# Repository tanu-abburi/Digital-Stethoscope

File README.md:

# Digital Stethoscope  
A **digital stethoscope** that amplifies, filters, and digitally processes heart sounds for enhanced diagnostics and remote monitoring.  
## Project Outline
We intend on developing a digital stethoscope system which includes an acoustic sensor that is attached to the processing unit, which will catch the signal, amplify it using an amplifier circuit using an op amp TL082.
The amplified signal is then sent to the ATMEGA328-P, which then converts the analog signal to a digital one ,which is then displayed as a waveform on the LCD TFT screen.  We intend to 3D printing an enclosure which will offer mechanical support and keep the enclosure compact.
## Working
The custom acoustic sensor is positioned on a pulse point of the body.
The sound is transmitted to an amplifier circuit via a condenser microphone. 
The amplified signal is then sent to the A0 ADC pin of the  ATmega328P microcontroller, where it is processed and displayed on the LCD screen.
On the LCD screen, we display to waveform as well as the calculated BPM rate .

## Simulation Results

## Schematic

## PCB Layout and 3D view

##  Team Members  
- **Ashley Ann Benoy** - EE23BTECH11204  
- **Avani Chouhan** - EE23BTECH11205  
- **Abburi Tanusha** - EE23BTECH11201  
- **Manugunta Meghana Sai** - EE23BTECH11212  
- **Muthyala Nikhitha Sri** - EE23BTECH11213

## System

## References
https://circuitdigest.com/microcontroller-projects/diy-wireless-digital-stethoscope

https://people.ece.cornell.edu/land/courses/ece4760/FinalProjects/s2012/myw9_gdd9/myw9_gdd9/

https://circuitdigest.com/fullimage?i=circuitdiagram_mic/Wireless-Stethoscope-Circuit.png

https://www.youtube.com/watch?v=w6MbM_f_7Uo

https://www.youtube.com/watch?v=QSXJG3opua8&t=3s

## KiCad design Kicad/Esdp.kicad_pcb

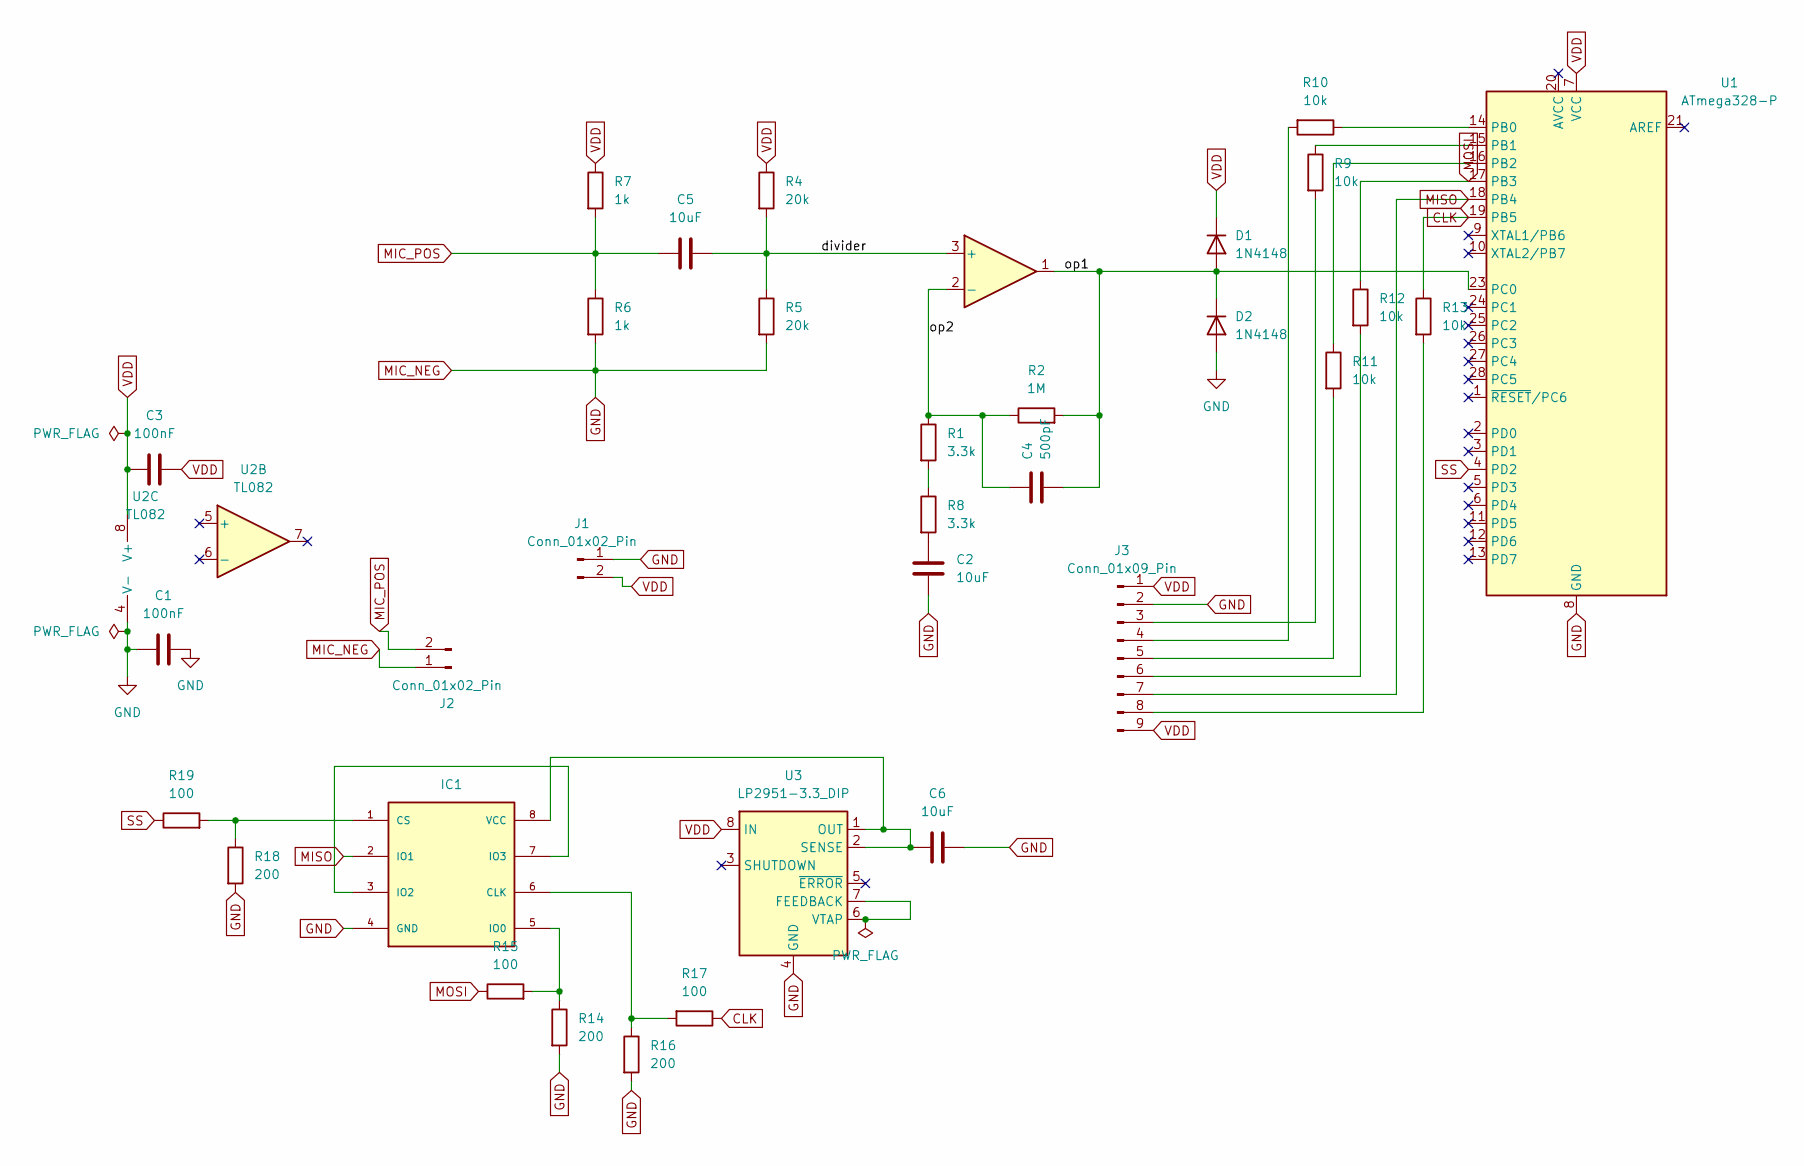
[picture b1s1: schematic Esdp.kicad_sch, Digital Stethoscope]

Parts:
C1, C3: 100nF; C_1206_3216Metric
C2, C5, C6: 10uF; C_1206_3216Metric
C4: 500pF; C_0805_2012Metric
D1, D2: 1N4148; D_DO-35_SOD27_P7.62mm_Horizontal
IC1: W25Q80DVSSIG; SOIC8-FLASH
J1: Conn_01x02_Pin; PinSocket_1x02_P1.27mm_Vertical
J2: Conn_01x02_Pin; TerminalBlock_Phoenix_MPT-0,5-2-2.54_1x02_P2.54mm_Horizontal
J3: Conn_01x09_Pin; PinSocket_1x09_P1.27mm_Vertical
R1, R8: 3.3k; R_1206_3216Metric
R2: 1M; R_1206_3216Metric
R4, R5: 20k; R_0603_1608Metric
R6, R7: 1k; R_0805_2012Metric
R9, R10, R11, R12, R13: 10k; R_0805_2012Metric
R14, R16, R18: 200; R_1206_3216Metric
R15, R17, R19: 100; R_0805_2012Metric
U1: ATmega328-P; DIP-28_W7.62mm_Socket
U2: TL082; DIP-8_W7.62mm_LongPads
U3: LP2951-3.3_DIP; DIP-8_W7.62mm

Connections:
/divider: C5.1, R4.2, R5.1, U2.3 (+)
/op1: C4.2, D1.2 (A), D2.1 (K), R2.2, U1.23 (PC0), U2.1
/op2: C4.1, R1.1, R2.1, U2.2 (-)
CLK: R13.1, R17.1, U1.19 (PB5)
GND: C1.1, C1.2, C2.2, C6.1, D2.2 (A), IC1.4 (GND), J1.1, J2.1, J3.2, R5.2, R6.2, R14.2, R16.2, R18.2, U1.8 (GND), U1.22 (GND), U2.4 (V-), U3.4 (GND)
MIC_POS: C5.2, J2.2, R6.1, R7.2
MISO: IC1.2 (IO1), J3.7, U1.18 (PB4)
MOSI: R12.1, R15.1, U1.17 (PB3)
unnamed: C2.1, R8.2
unnamed: IC1.6 (CLK), R16.1, R17.2
unnamed: IC1.1 (CS), R18.1, R19.2
unnamed: IC1.5 (IO0), R14.1, R15.2
unnamed: IC1.3 (IO2), IC1.7 (IO3)
unnamed: C6.2, IC1.8 (VCC), U3.1 (OUT), U3.2 (SENSE)
unnamed: J3.3, R9.2
unnamed: J3.4, R10.2
unnamed: J3.5, R11.2
unnamed: J3.6, R12.2
unnamed: J3.8, R13.2
unnamed: R1.2, R8.1
unnamed: R10.1, U1.14 (PB0)
unnamed: R9.1, U1.15 (PB1)
unnamed: R11.1, U1.16 (PB2)
unnamed: U3.6 (VTAP), U3.7 (FEEDBACK)
SS: R19.1, U1.4 (PD2)
VDD: C3.1, C3.2, D1.1 (K), J1.2, J3.1, J3.9, R4.1, R7.1, U1.7 (VCC), U2.8 (V+), U3.8 (IN)

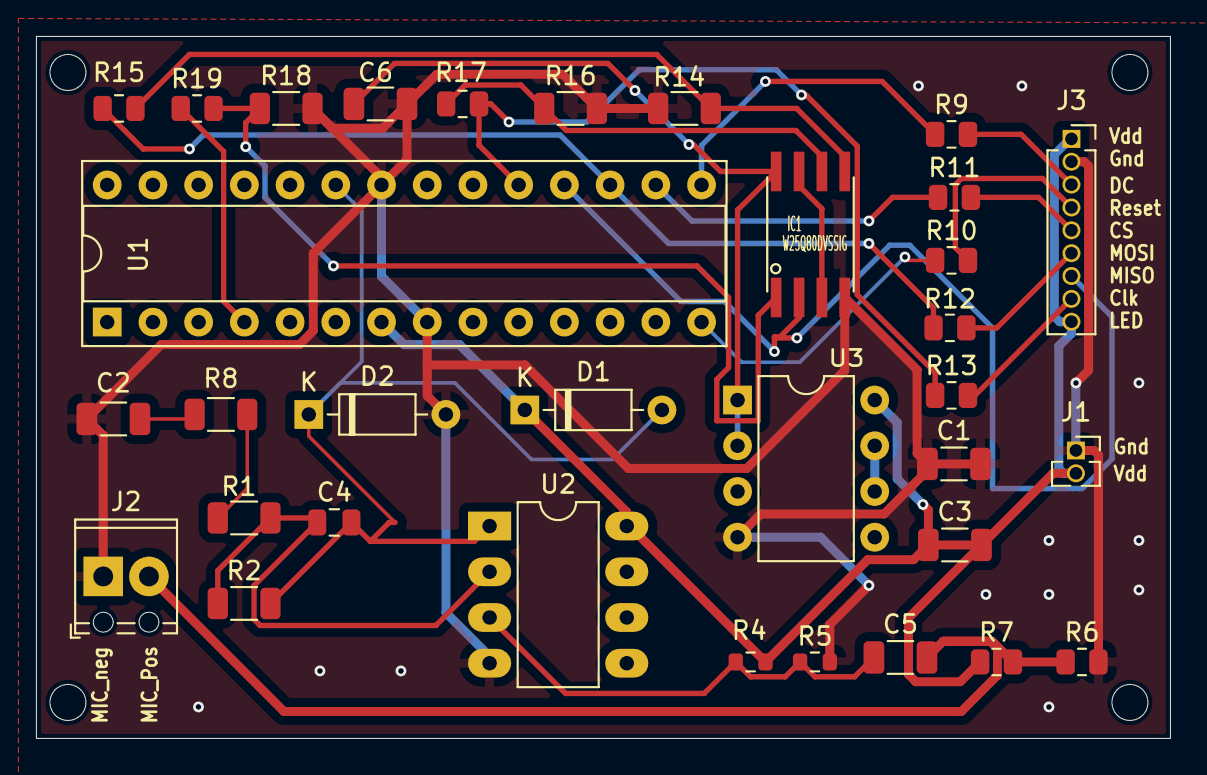
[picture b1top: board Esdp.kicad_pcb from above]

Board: 2 copper layers, 63.0 x 39.0 mm, 33 parts (0 on the bottom side), 26 nets.

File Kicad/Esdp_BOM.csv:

"Reference","Value","Datasheet","Footprint","Qty","DNP"
"C1,C3","100nF","~","Capacitor_SMD:C_1206_3216Metric","2",""
"C2,C5,C6","10uF","~","Capacitor_SMD:C_1206_3216Metric","3",""
"C4","500pF","~","Capacitor_SMD:C_0805_2012Metric","1",""
"D1,D2","1N4148","https://assets.nexperia.com/documents/data-sheet/1N4148_1N4448.pdf","Diode_THT:D_DO-35_SOD27_P7.62mm_Horizontal","2",""
"IC1","W25Q80DVSSIG","","W25Q80DVSSIG:SOIC8-FLASH","1",""
"J1","Conn_01x02_Pin","~","Connector_PinSocket_1.27mm:PinSocket_1x02_P1.27mm_Vertical","1",""
"J2","Screw_Terminal_01x02","~","TerminalBlock_Phoenix:TerminalBlock_Phoenix_MPT-0,5-2-2.54_1x02_P2.54mm_Horizontal","1",""
"J3","Conn_01x09_Pin","~","Connector_PinSocket_1.27mm:PinSocket_1x09_P1.27mm_Vertical","1",""
"R1,R8","3.3k","~","Resistor_SMD:R_1206_3216Metric","2",""
"R2","1M","~","Resistor_SMD:R_1206_3216Metric","1",""
"R3,R9,R10,R11,R12,R13","10k","~","Resistor_SMD:R_0805_2012Metric","6",""
"R4,R5","20k","~","Resistor_SMD:R_0603_1608Metric","2",""
"R6,R7","1k","~","Resistor_SMD:R_0805_2012Metric","2",""
"R14,R16,R18","200","~","Resistor_SMD:R_1206_3216Metric","3",""
"R15,R17,R19","100","~","Resistor_SMD:R_0805_2012Metric","3",""
"U1","ATmega328-P","http://ww1.microchip.com/downloads/en/DeviceDoc/ATmega328_P%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","Package_DIP:DIP-28_W7.62mm_Socket","1",""
"U2","TL082","http://www.ti.com/lit/ds/symlink/tl081.pdf","Package_DIP:DIP-8_W7.62mm_LongPads","1",""
"U3","LP2951-3.3_DIP","http://www.ti.com/lit/ds/symlink/lp2951.pdf","Package_DIP:DIP-8_W7.62mm","1",""

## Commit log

2025-02-16 Create guide
2025-02-18 Create new
2025-05-11 Rename Esdp.zip to Kicad/Esdp.zip
2025-05-16 Create Gerber
2025-05-16 Create Description
2025-05-16 Create images
2025-05-16 Update and rename new to code
2025-05-17 Create Video reference
